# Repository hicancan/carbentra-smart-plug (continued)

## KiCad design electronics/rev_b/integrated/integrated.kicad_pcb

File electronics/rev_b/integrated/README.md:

# CARBENTRA · CARBENTRA-P16-EVT-B electronics

**Routed engineering development candidate. Fabrication and energization remain on hold.**

This revision integrates edge control, isolated metering, post-switch AC-presence feedback and an independent thermal permission latch on a 100 × 85 mm, four-layer board. It retains a separate 12 × 12 mm thermal pickup head and in-enclosure main protection components. The proposal is a single 220 VAC ±10% socket platform with commissioned load profiles, not a universal plug-hole adapter or an unconditional 16 A motor-switching rating.

## Open these files first

- `integrated.kicad_pro`, `integrated.kicad_sch`, `integrated.kicad_pcb`: editable native project
- `exports/schematic.pdf`: six readable functional/assembly sheets
- `electrical_bom.csv` and `electrical_manifest.json`: numbered pins, real candidates and primary-source links
- `ELECTRICAL_SOURCE.md`: circuit and interface definition
- `POWER_CURRENT_REVIEW.md`: current paths, copper-loss calculations and fault limits
- `RAIL_BUDGET.md`: the IRM-10-5 supply reservation and temperature derating
- `validation/final_summary.json`: current board-hashed verification results

The final main board has **101 electrical items plus four mounting footprints**. Of those electrical items, 99 have physical component bodies and two are zero-height test pads. There are 321 unique numbered main-board pad keys. The full six-sheet assembly graph has 348 numbered terminals, including the remote head, harness models and off-board protection.

## What is implemented

- ESP32-C3-WROOM-02U, external antenna connection, programming/boot controls, local button, status LED and polled TMP102 board temperature
- IRM-10-5 isolated 5 V supply and AP63203 3.3 V buck; conservative concurrent reservation 3.885 W, with manufacturer derating kept explicit
- Four-terminal 1 mΩ shunt, graded voltage divider, ATM90E26, 8.192 MHz oscillator, ISO6741 SPI isolation and an R05CT isolated supply for the mains-referenced metering domain
- ACPL-K376 post-switch AC-presence detector; this reports voltage presence, not a certified absence-of-voltage indication or mechanical contact position
- Remote TMP302 threshold sensor, power supervisor, set-dominant hardware trip behavior, local physical rearm edge and independent coil-supply gating
- Defined main fuse → thermal link → protected line → shunt → relay → output path, plus continuous unswitched PE outside the PCB
- Fully connected four-layer copper, an isolated logic return plane, mechanical hole keepouts and modeled through-hole lead reserves

`HOT_GND` is **line potential**, never PE or isolated logic ground. The main fuse is SHF 8020.5080 with two CQP 8040.0003 clips on a retained insulating carrier. F501 is a separate 1 A auxiliary-supply fuse. The thermal link responds to temperature; it is not an overcurrent fuse. There is no active current-limiting circuit. The software reference does not establish an independent, commissioned current-duration trip.

## Verification and its boundary

The canonical results are `final_drc.rpt`, `final_erc.rpt`, `final_pin_audit.json`, `final_isolation.json` and `final_source_graph.json` under `validation/`. Historical intermediate results are retained in Git; only current canonical reports are kept in the working tree.

- Native DRC: zero violations, zero unconnected items, zero footprint errors
- ERC: zero errors and zero warnings
- Independent schematic-to-PCB pin comparison: all 321 main-board keys match
- Independent projected isolation audit: includes all copper layers, unused isolator pins and the complete conservative ground-plane outline; minimum component land gap 8.10 mm; routed copper/plane targets at least 8.4 mm
- Negative controls: a synthetic 6 mm gap is rejected by the supported KiCad rule, and a shifted hot pad is rejected by the independent checker
- Rebuild: placement/net geometry is checked before the saved copper recipe is replayed; no undocumented autorouter state is required

**These are digital checks, not manufactured insulation or current ratings.** The 8.10 mm component-land minimum has only 0.10 mm nominal reserve above the preliminary 8 mm rule. Finished land geometry, solder spread, contamination, creepage, material group, altitude, dielectric construction and measurement tolerances still require a qualified insulation design review. The 2.5 mm open-contact and 3 mm neutral functional rules are preliminary engineering constraints, not a standards-compliance claim.

A negative-control investigation found that earlier JavaScript-style `NetName.startsWith(...)` conditions were not enforced by KiCad. This revision uses supported wildcard comparisons and records both the failing old control and corrected control. The frozen EVT-A baseline was not rewritten; see `../BASELINE_RULE_LIMITATION.md`.

## Physical exports

- `exports/placement_assembly.step`: 144 valid solids for component/body/lead fit checking
- `exports/integrated_assembly.step`, `.FCStd`, `.obj`: 3133 valid solids including actual native pads, traces and vias
- `exports/component_envelopes.json`: component and lead bounds
- `exports/remote_head_assembled.step`, `.obj`, `.json`: 19 valid head solids in final assembly coordinates, with an explicit proper rigid transform and source hash

Main-board exports use millimetres, centered XY, board bottom at local z=0; the mechanical assembly translates MainB by +11.5 mm in Z. The HeadB export is already in assembly coordinates and must not receive that translation. Its pickup copper face is at z=43.5 mm. Copper is raised/colored for inspection; solder mask/tenting and detailed manufacturer body geometry are not qualified by the visualization. Native KiCad copper and plane files remain authoritative.

## Required release gates

1. Confirm the applicable plug/socket standard, market, altitude, insulation class and actual 198–242 VAC operating requirement. The 264 VAC calculation point is measurement headroom only.
2. Obtain actual prospective fault current, upstream breaker curve and fuse total-clearing data. SHF's stated 760 A²s is typical **melting** I²t at 10× rated current, not an upper bound on total let-through. Qualify every trace, via, shunt, terminal, collector, wire and joint accordingly.
3. Test enclosed 16 A temperature rise and short-circuit containment. The copper-loss model and 70 µm outer-copper proposal are not a finished-board current rating. Verify plating, current sharing, solder joints, fuse-clip retention and enclosure heat.
4. Obtain the intended load's steady current, locked-rotor/inrush waveform, repetition rate and switching duty. The relay's resistive rating does not release a 16 A compressor, transformer or capacitive load.
5. Calibrate voltage/current/power/energy with traceable references and signed profile data. Verify shunt polarity, startup checksums, timing, waveform range and overrange behavior. Firmware contract: `../FIRMWARE_CONTRACT.md`.
6. Test thermal pickup lag, threshold spread, pressure/aging of the insulating pad, sensor/pigtail failures, slow power ramps, local rearm and welded contacts. Ideal latch tests cannot prove this physical behavior.
7. Complete EMC/surge/EFT, RF/antenna integration, dielectric/impulse, creepage/clearance, abnormal-operation, mechanical gauge/retention and production reliability testing.
8. Obtain board-house approval of the four-layer stack, 0.20 mm finished signal-via drills, via-in-pad/tenting/fill process and all authored land patterns before any fabrication release.

Power restoration starts de-energized and requires the defined thermal rearm/commissioning sequence. Runtime unknown-load, stale-meter and offline behavior must follow the commissioned policy; they are not universal instructions for abrupt power removal. See the repository's system/network and sensor documentation.

## Rebuild

Use `bash scripts/rebuild.sh --no-geometry` for a source/copper/verification rebuild, or omit the option to regenerate geometry. KiCad 9, its standard libraries, system Python with pcbnew/NumPy, FreeCAD, Inkscape, ReportLab and pypdf are required. The script validates geometry against `routing_recipe.json` before applying copper and then reruns the independent checks. Local vendor-PDF research caches are not required deliverables; official URLs remain in the BOM and authored notes.

## Rear termination integration correction

The corrected front/rear polarity exposed an assembly-level clearance problem that native PCB-domain DRC could not detect. The rear L tail was lowered by the mechanical design, the nearby +5 V and +3.3 V branches were rerouted, and the internal GND plane was recessed. All component placements remain fixed. `validation/rear_termination.json` independently checks the resulting rear metal against native isolated copper, including the conservative entire plane outline. The nominal minimum is 8.5166 mm, versus an 8.4 mm design check. This is not a tolerance-qualified clearance or creepage result. The complete mechanical insulation-domain report remains a separate release gate.

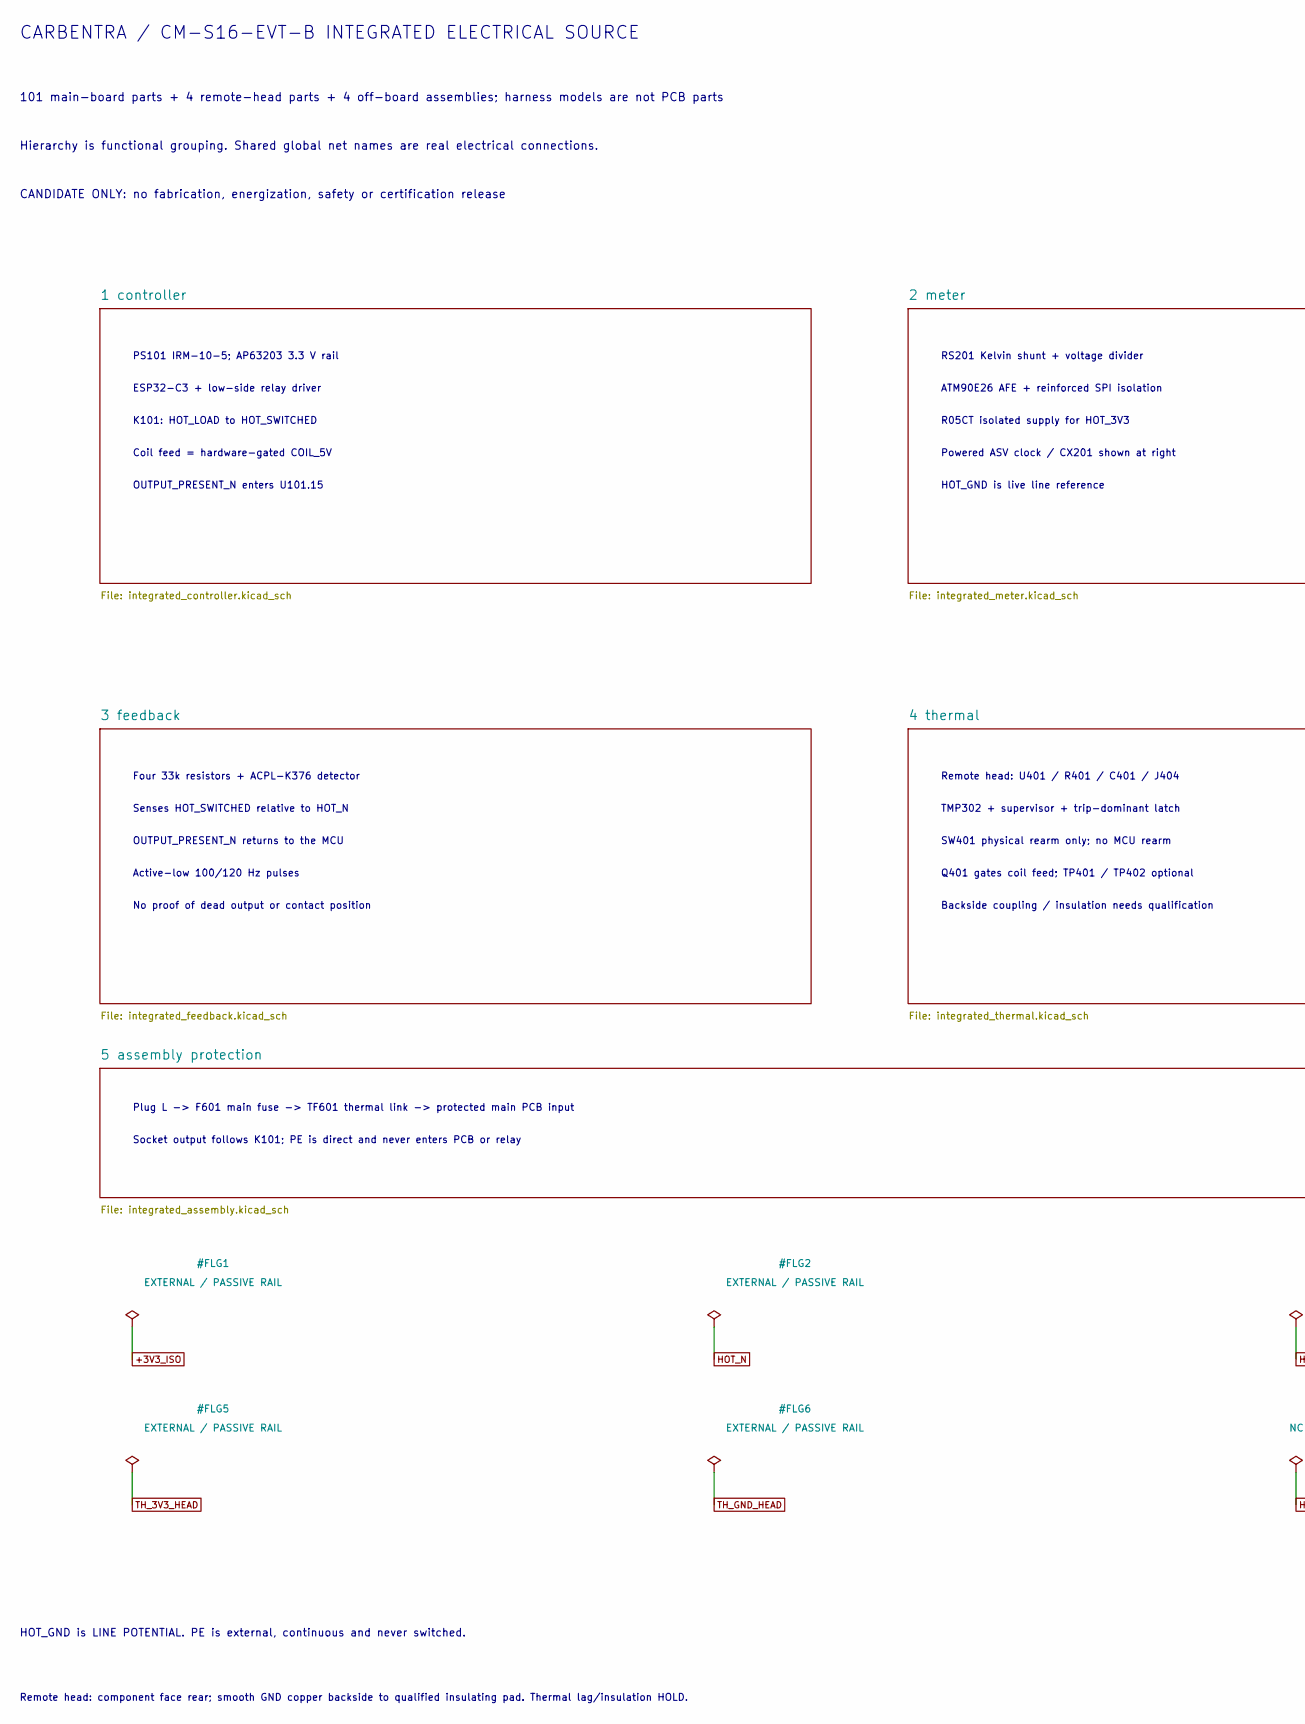
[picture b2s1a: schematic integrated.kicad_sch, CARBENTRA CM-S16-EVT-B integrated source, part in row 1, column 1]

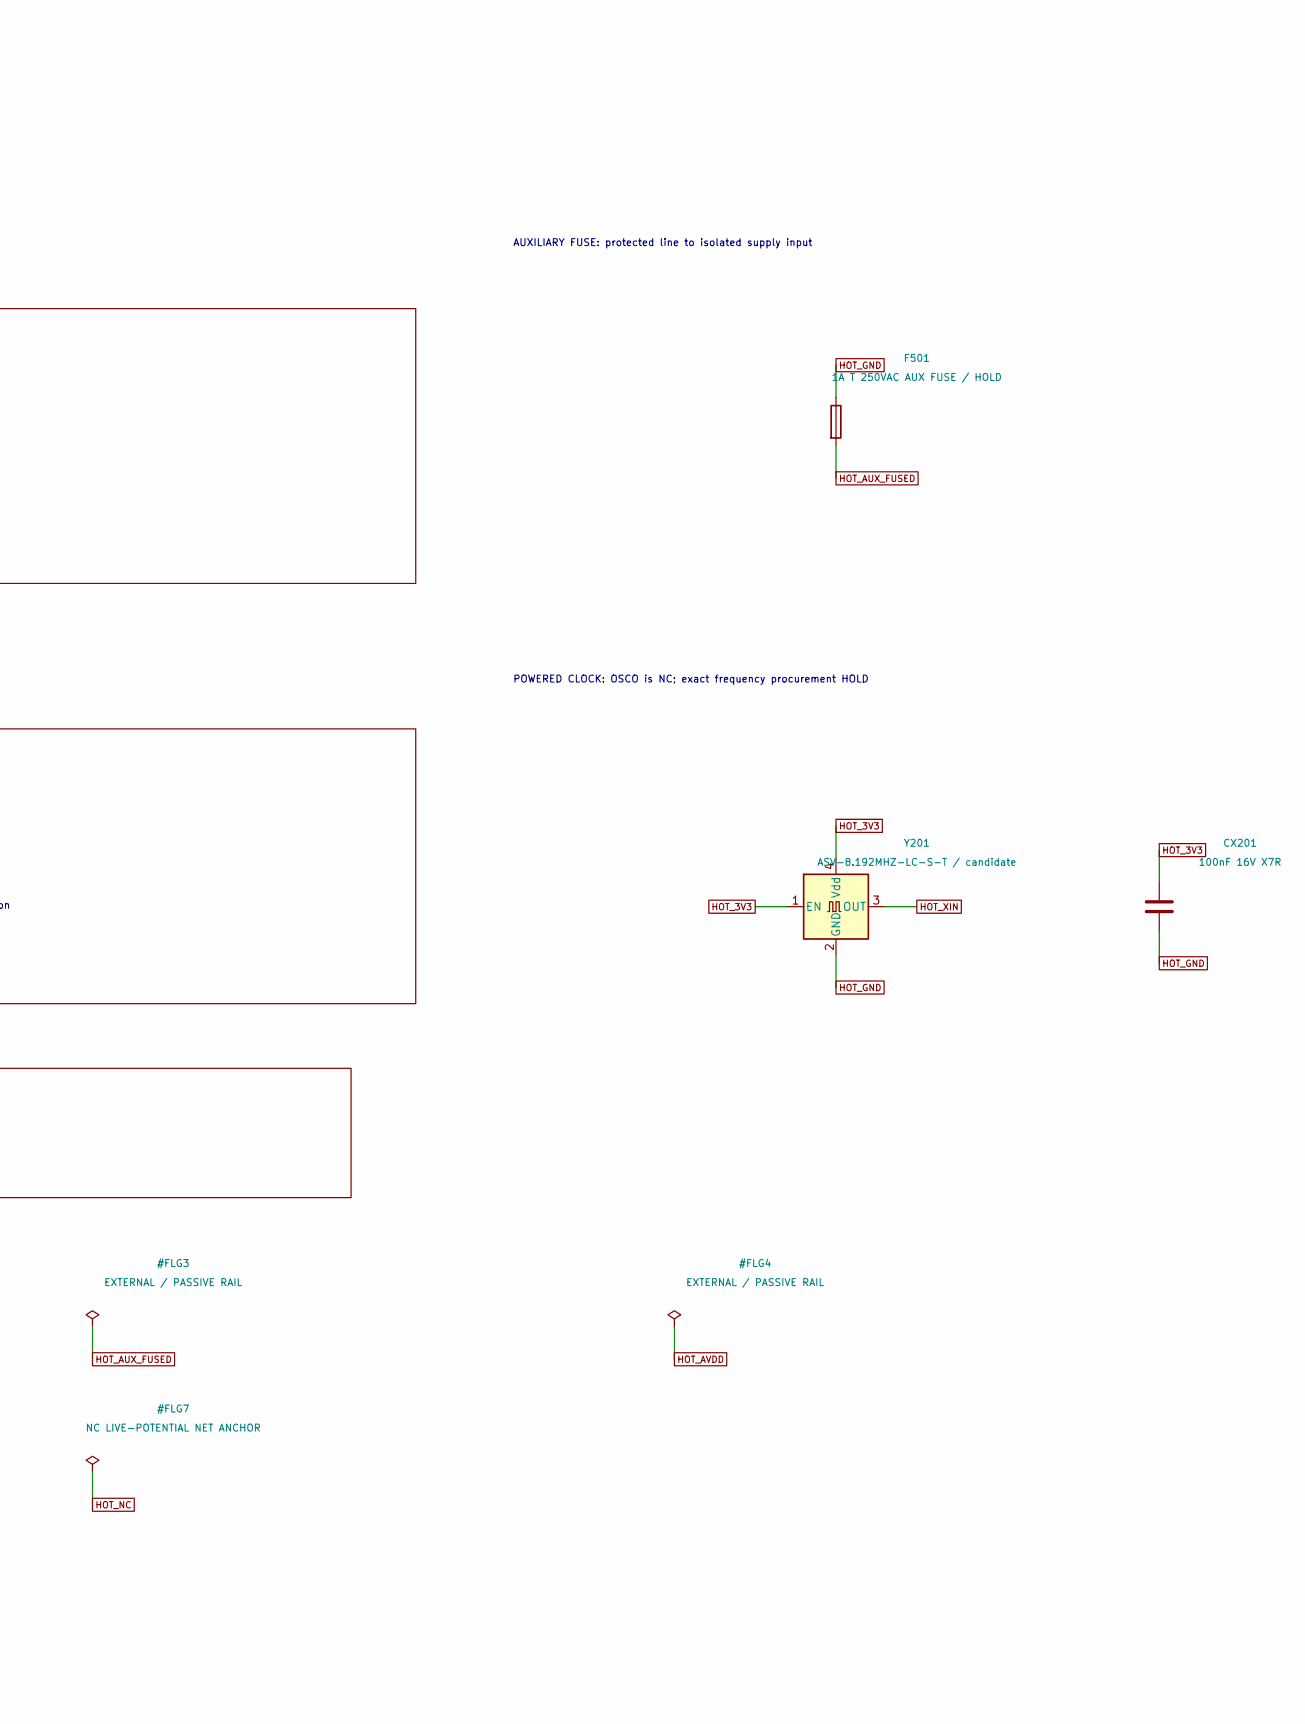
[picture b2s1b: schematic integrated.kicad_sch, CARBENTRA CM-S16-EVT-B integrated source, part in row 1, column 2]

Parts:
CX201: 100nF 16V X7R; C_0805_2012Metric
F501: 1A T 250VAC AUX FUSE / HOLD; Fuse_215_Axial_P30mm
Y201: ASV-8.192MHZ-LC-S-T / candidate; Oscillator_SMD_Abracon_ASV-4Pin_7.0x5.1mm

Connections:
HOT_3V3: CX201.1, Y201.1 (EN), Y201.4 (Vdd); also elsewhere on the board
HOT_AUX_FUSED: F501.2; also elsewhere on the board
HOT_GND: CX201.2, F501.1, Y201.2 (GND); also elsewhere on the board
HOT_XIN: Y201.3 (OUT); also elsewhere on the board

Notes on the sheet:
PS101 IRM-10-5; AP63203 3.3 V rail
ESP32-C3 + low-side relay driver
K101: HOT_LOAD to HOT_SWITCHED
Coil feed = hardware-gated COIL_5V
OUTPUT_PRESENT_N enters U101.15
RS201 Kelvin shunt + voltage divider
ATM90E26 AFE + reinforced SPI isolation
R05CT isolated supply for HOT_3V3
Powered ASV clock / CX201 shown at right
HOT_GND is live line reference
Four 33k resistors + ACPL-K376 detector
Senses HOT_SWITCHED relative to HOT_N
OUTPUT_PRESENT_N returns to the MCU
Active-low 100/120 Hz pulses
No proof of dead output or contact position
Remote head: U401 / R401 / C401 / J404
TMP302 + supervisor + trip-dominant latch
SW401 physical rearm only; no MCU rearm
Q401 gates coil feed; TP401 / TP402 optional
Backside coupling / insulation needs qualification
Plug L -> F601 main fuse -> TF601 thermal link -> protected main PCB input
Socket output follows K101; PE is direct and never enters PCB or relay
CARBENTRA / CM-S16-EVT-B INTEGRATED ELECTRICAL SOURCE
101 main-board parts + 4 remote-head parts + 4 off-board assemblies; harness models are not PCB parts
Hierarchy is functional grouping. Shared global net names are real electrical connections.
CANDIDATE ONLY: no fabrication, energization, safety or certification release
AUXILIARY FUSE: protected line to isolated supply input
POWERED CLOCK: OSCO is NC; exact frequency procurement HOLD
HOT_GND is LINE POTENTIAL. PE is external, continuous and never switched.
Remote head: component face rear; smooth GND copper backside to qualified insulating pad. Thermal lag/insulation HOLD.

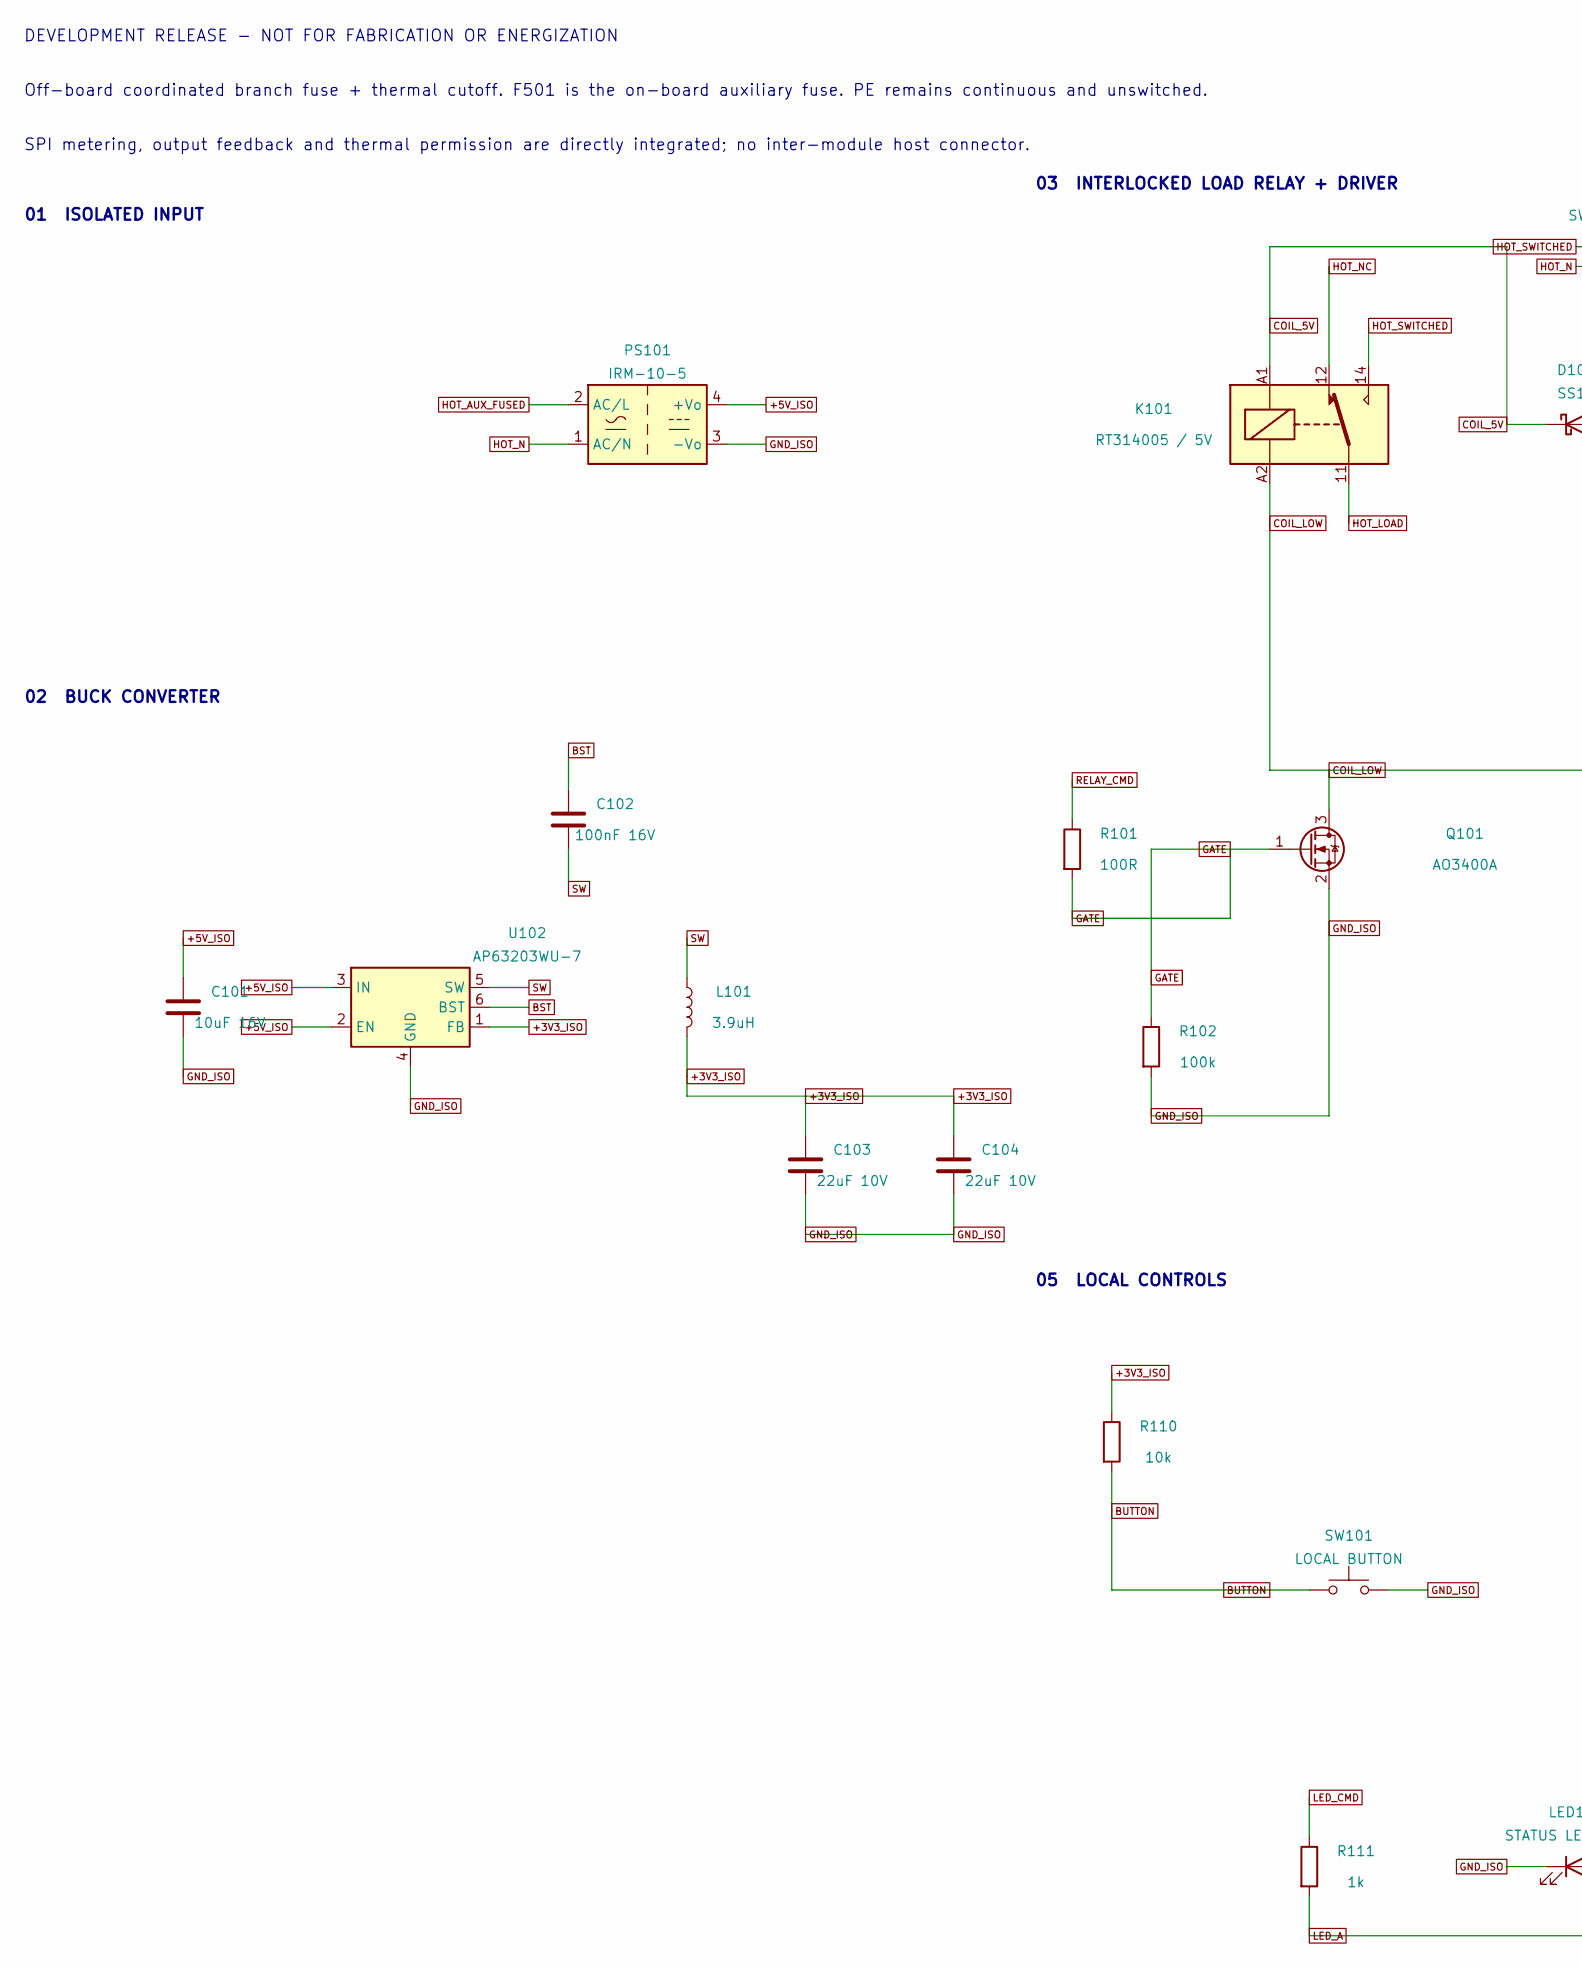
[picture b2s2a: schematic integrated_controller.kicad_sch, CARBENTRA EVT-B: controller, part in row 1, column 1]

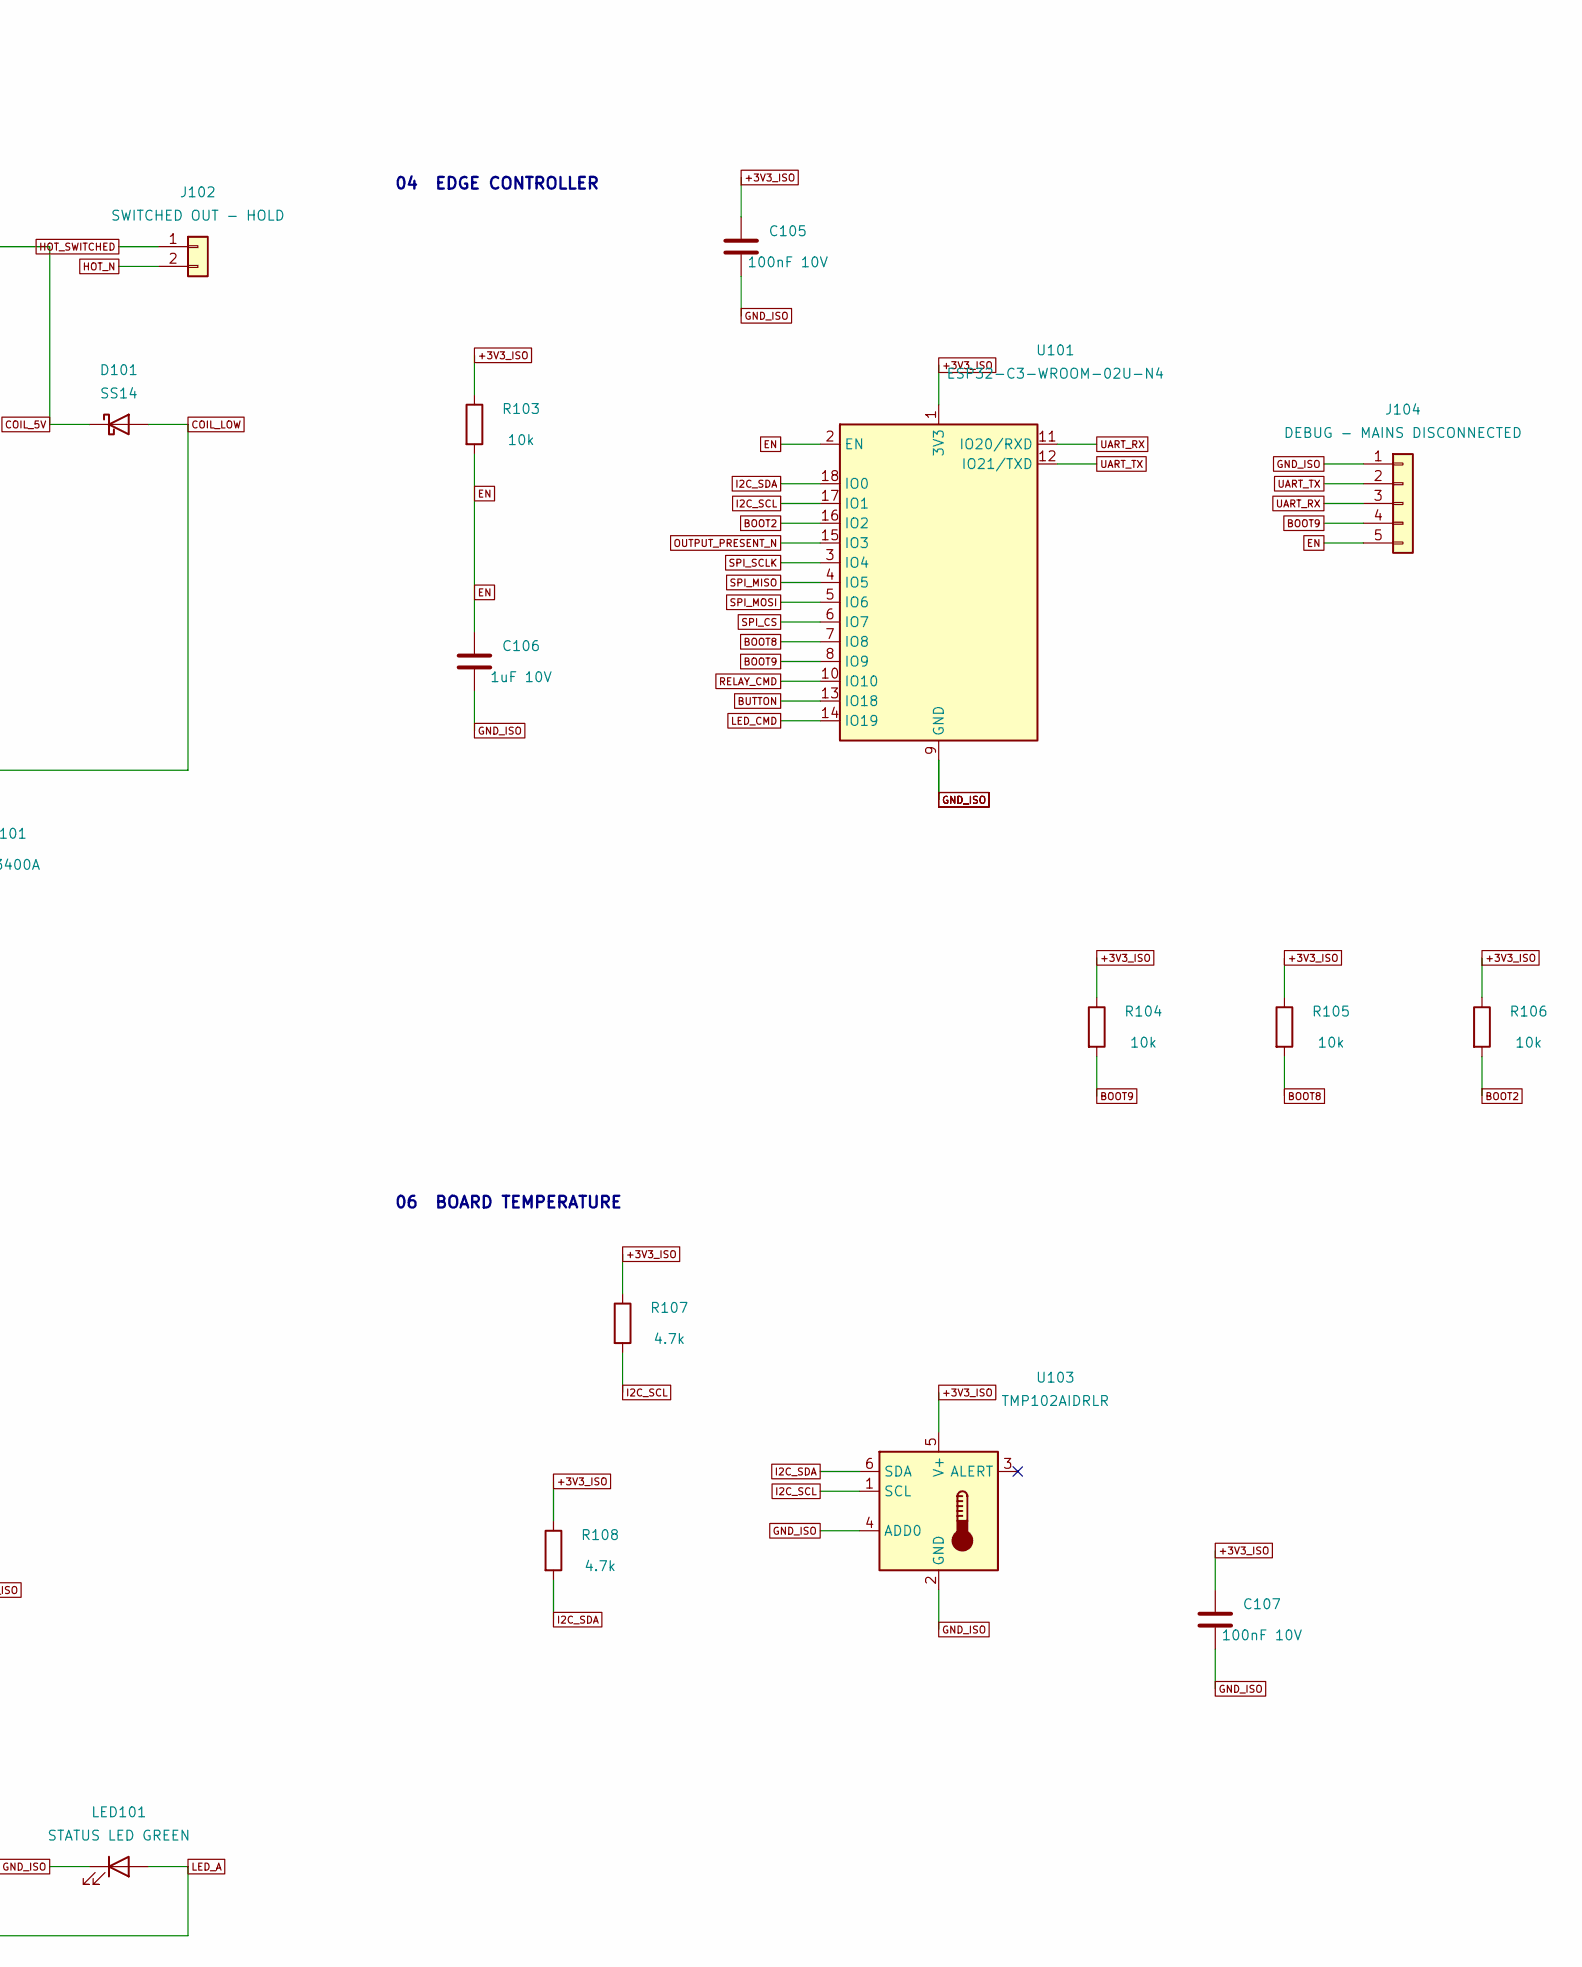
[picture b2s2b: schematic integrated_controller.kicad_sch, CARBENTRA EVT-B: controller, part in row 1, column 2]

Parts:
C101: 10uF 16V; C_0805_2012Metric
C102: 100nF 16V; C_0805_2012Metric
C103, C104: 22uF 10V; C_0805_2012Metric
C105, C107: 100nF 10V; C_0805_2012Metric
C106: 1uF 10V; C_0805_2012Metric
D101: SS14; D_SMA
J102: SWITCHED OUT - HOLD; MKDS5_2_7p62
J104: DEBUG - MAINS DISCONNECTED; PinHeader_1x05_P2.54mm_Vertical
K101: RT314005 / 5V; Relay_SPDT_Schrack-RT1-16A-FormC_RM5mm
L101: 3.9uH; L_Bourns-SRN4018
LED101: STATUS LED GREEN; LED_D3.0mm
PS101: IRM-10-5; IRM10_Controller_Candidate
Q101: AO3400A; SOT-23
R101: 100R; R_0603_1608Metric
R102: 100k; R_0603_1608Metric
R103, R104, R105, R106, R110: 10k; R_0603_1608Metric
R107, R108: 4.7k; R_0603_1608Metric
R111: 1k; R_0603_1608Metric
SW101: LOCAL BUTTON; SW_PUSH_6mm
U101: ESP32-C3-WROOM-02U-N4; ESP32-C3-WROOM-02U
U102: AP63203WU-7; TSOT-23-6
U103: TMP102AIDRLR; SOT-563

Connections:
+3V3_ISO: C103.1, C104.1, C105.1, C107.1, L101.2, R103.1, R104.1, R105.1, R106.1, R107.1, R108.1, R110.1, U101.1 (3V3), U102.1 (FB), U103.5 (V+); also elsewhere on the board
+5V_ISO: C101.1, PS101.4 (+Vo), U102.2 (EN), U102.3 (IN); also elsewhere on the board
BOOT2: R106.2, U101.16 (IO2)
BOOT8: R105.2, U101.7 (IO8)
BOOT9: J104.4, R104.2, U101.8 (IO9)
BST: C102.1, U102.6 (BST)
BUTTON: R110.2, SW101.1, U101.13 (IO18)
COIL_5V: D101.1 (K), K101.A1; also elsewhere on the board
COIL_LOW: D101.2 (A), K101.A2, Q101.3 (D)
EN: C106.1, J104.5, R103.2, U101.2 (EN)
GATE: Q101.1 (G), R101.2, R102.1
GND_ISO: C101.2, C103.2, C104.2, C105.2, C106.2, C107.2, J104.1, LED101.1 (K), PS101.3 (-Vo), Q101.2 (S), R102.2, SW101.2, U101.9 (GND), U101.19 (GND), U102.4 (GND), U103.2 (GND), U103.4 (ADD0); also elsewhere on the board
HOT_AUX_FUSED: PS101.2 (AC/L); also elsewhere on the board
HOT_LOAD: K101.11; also elsewhere on the board
HOT_N: J102.2, PS101.1 (AC/N); also elsewhere on the board
HOT_NC: K101.12
HOT_SWITCHED: J102.1, K101.14; also elsewhere on the board
I2C_SCL: R107.2, U101.17 (IO1), U103.1 (SCL)
I2C_SDA: R108.2, U101.18 (IO0), U103.6 (SDA)
LED_A: LED101.2 (A), R111.2
LED_CMD: R111.1, U101.14 (IO19)
OUTPUT_PRESENT_N: U101.15 (IO3); also elsewhere on the board
RELAY_CMD: R101.1, U101.10 (IO10)
SPI_CS: U101.6 (IO7); also elsewhere on the board
SPI_MISO: U101.4 (IO5); also elsewhere on the board
SPI_MOSI: U101.5 (IO6); also elsewhere on the board
SPI_SCLK: U101.3 (IO4); also elsewhere on the board
SW: C102.2, L101.1, U102.5 (SW)
UART_RX: J104.3, U101.11 (IO20/RXD)
UART_TX: J104.2, U101.12 (IO21/TXD)

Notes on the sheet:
DEVELOPMENT RELEASE - NOT FOR FABRICATION OR ENERGIZATION
Off-board coordinated branch fuse + thermal cutoff. F501 is the on-board auxiliary fuse. PE remains continuous and unswitched.
SPI metering, output feedback and thermal permission are directly integrated; no inter-module host connector.
01 ISOLATED INPUT
02 BUCK CONVERTER
03 INTERLOCKED LOAD RELAY + DRIVER
04 EDGE CONTROLLER
05 LOCAL CONTROLS
06 BOARD TEMPERATURE
